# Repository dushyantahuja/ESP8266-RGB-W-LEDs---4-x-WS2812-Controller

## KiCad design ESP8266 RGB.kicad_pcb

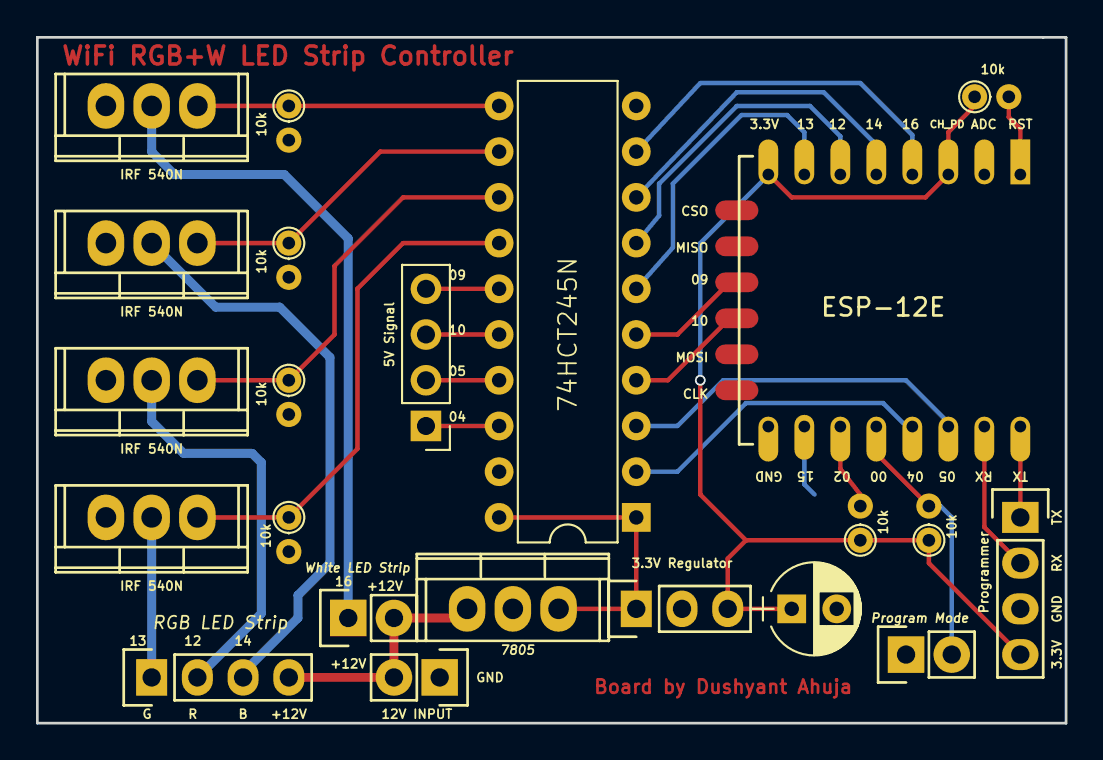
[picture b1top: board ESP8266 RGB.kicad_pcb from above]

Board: 2 copper layers, 57.2 x 38.1 mm, 22 parts (0 on the bottom side), 29 nets.

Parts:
.1: ESP-12E
C1: CP; CP_Radial_D5.0mm_P2.50mm
P1: White LED Strip; Socket_Strip_Straight_1x02
P2: RGB LED Strip; Socket_Strip_Straight_1x04
P3: 3.3V Regulator; Socket_Strip_Straight_1x03
P4: Programmer; Socket_Strip_Straight_1x04
P6: 12V INPUT; Socket_Strip_Straight_1x02
P7: 5V Signal; Socket_Strip_Straight_1x04_Pitch2.54mm
PRGM1: Program Mode; Socket_Strip_Straight_1x02
Q1, Q2, Q3, Q4: IRF540N; TO-220
R1, R2, R3, R4, R5, R6, R7: 10k; R_Axial_DIN0204_L3.6mm_D1.6mm_P1.90mm_Vertical
U1: 74HCT245; DIP-20_W7.62mm
U2: 7805; TO-220

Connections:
+3V3: .1.3, .1.8, C1.1, P3.3, P4.4, R1.1, R2.1, R7.1
+5V: P3.1, U1.1, U1.20, U2.3
+12V: P1.2, P2.4, P6.2, U2.1
A0: .1.13, U1.2
A1: .1.14, U1.3
A2: .1.20, U1.4
A3: .1.19, U1.5
B0: P7.1, U1.18
B1: P7.2, U1.17
B2: P7.3, U1.16
B3: P7.4, U1.15
GND: .1.10, C1.2, P3.2, P4.3, P6.1, PRGM1.1, Q1.3, Q2.3, Q3.3, Q4.3, R3.2, R4.2, R5.2, R6.2, U1.19, U2.2
unnamed: .1.1, R1.2
unnamed: .1.4, U1.9
unnamed: .1.5, U1.8
unnamed: .1.6, U1.7
unnamed: .1.7, U1.6
unnamed: .1.11, R7.2
unnamed: .1.12, PRGM1.2, R2.2
unnamed: .1.15, P4.2
unnamed: .1.16, P4.1
unnamed: P1.1, Q1.2
unnamed: P2.1, Q4.2
unnamed: P2.2, Q3.2
unnamed: P2.3, Q2.2
unnamed: Q1.1, R3.1, U1.11
unnamed: Q2.1, R4.1, U1.12
unnamed: Q3.1, R5.1, U1.13
unnamed: Q4.1, R6.1, U1.14

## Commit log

2017-03-10 :octocat: Added .gitattributes & .gitignore files
2017-03-11 Updated to connect GND pins for ESP-12 and 74HCT245N
    Somehow they got missed out in the board layout.
